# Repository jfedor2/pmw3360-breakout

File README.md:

# PMW3360 breakout board

This repository contains PCB design files for a breakout board for the PMW3360 optical mouse sensor.

The board doesn't do any level shifting so it only works with 3.3V logic.

The dimensions of the board are 22x34mm and the mounting holes are for M2 screws.

The files in the [fabrication](fabrication) folder can be used to order this board from JLCPCB with SMT assembly. The board you get includes everything except the actual sensor. If some of the specific components are out of stock, try to find an equivalent with the same package and parameters.

The sensor chip should be soldered on the top side (the side where all the other components are). The dot marks pin 1. The optic goes on the bottom side.

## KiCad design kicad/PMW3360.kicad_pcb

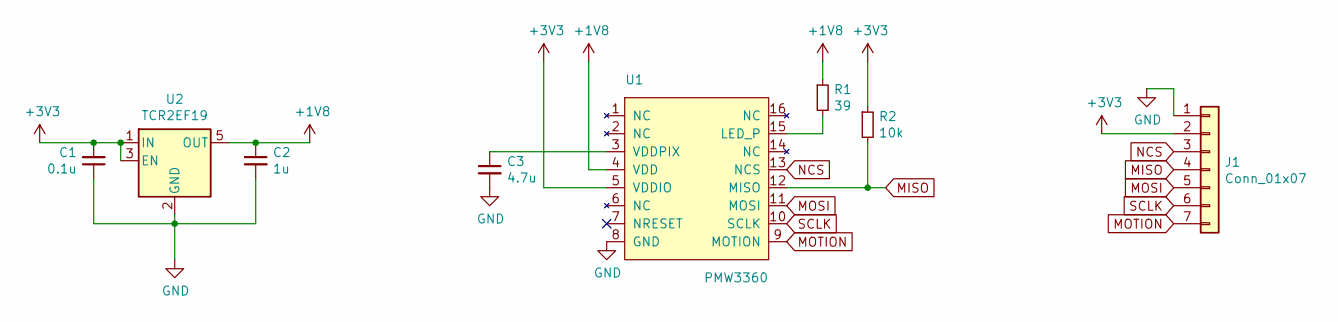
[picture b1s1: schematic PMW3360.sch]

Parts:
C1: 0.1u; C_0603_1608Metric; LCSC C14663
C2: 1u; C_0603_1608Metric; LCSC C15849
C3: 4.7u; C_0603_1608Metric; LCSC C19666
J1: Conn_01x07; PinHeader_1x07_P2.54mm_Vertical
R1: 39; R_0603_1608Metric; LCSC C137733
R2: 10k; R_0603_1608Metric; LCSC C25804
U1: PMW3360
U2: TCR2EF19; SOT-23-5; LCSC C146366

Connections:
+1V8: C2.1, R1.1, U1.4 (VDD), U2.5 (OUT)
+3V3: C1.2, J1.2, R2.1, U1.5 (VDDIO), U2.1 (IN), U2.3 (EN)
GND: C1.1, C2.2, C3.2, J1.1, U1.8 (GND), U2.2 (GND)
MISO: J1.4, R2.2, U1.12 (MISO)
MOSI: J1.5, U1.11 (MOSI)
MOTION: J1.7, U1.9 (MOTION)
NCS: J1.3, U1.13 (NCS)
unnamed: C3.1, U1.3 (VDDPIX)
unnamed: R1.2, U1.15 (LED_P)
SCLK: J1.6, U1.10 (SCLK)

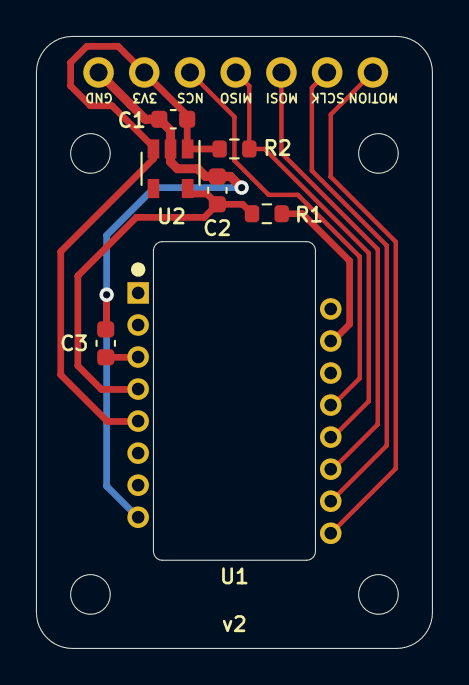
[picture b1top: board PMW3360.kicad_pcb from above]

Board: 2 copper layers, 22.0 x 34.0 mm, 8 parts (0 on the bottom side), 10 nets.

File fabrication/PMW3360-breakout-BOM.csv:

Comment,Designator,Footprint,LCSC
"0.1u","C1","Capacitor_SMD:C_0603_1608Metric","C14663"
"1u","C2","Capacitor_SMD:C_0603_1608Metric","C15849"
"4.7u","C3","Capacitor_SMD:C_0603_1608Metric","C19666"
"Conn_01x07","J1","Connector_PinHeader_2.54mm:PinHeader_1x07_P2.54mm_Vertical",""
"39","R1","Resistor_SMD:R_0603_1608Metric","C137733"
"10k","R2","Resistor_SMD:R_0603_1608Metric","C25804"
"PMW3360","U1","PMW3360:PMW3360",""
"TCR2EF19","U2","Package_TO_SOT_SMD:SOT-23-5","C146366"

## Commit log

2022-07-31 Add license
